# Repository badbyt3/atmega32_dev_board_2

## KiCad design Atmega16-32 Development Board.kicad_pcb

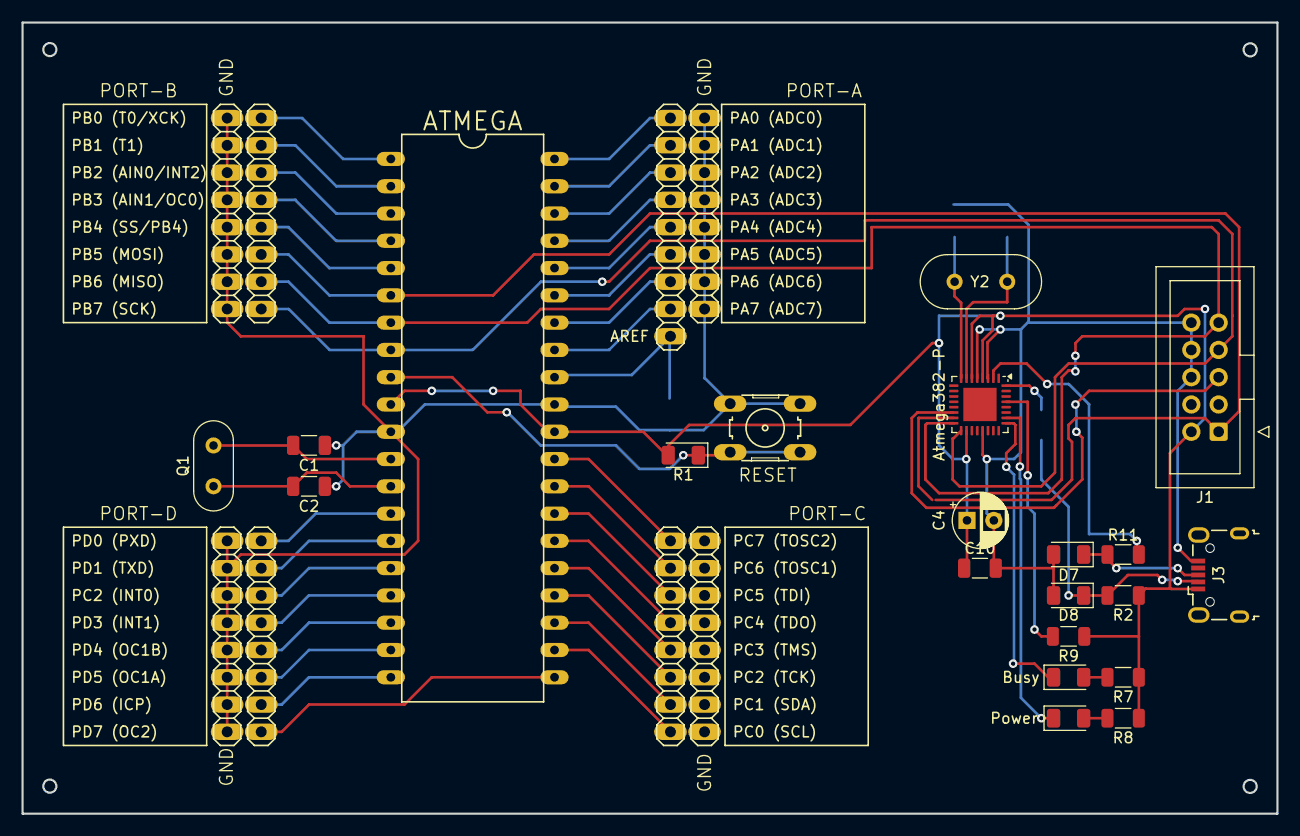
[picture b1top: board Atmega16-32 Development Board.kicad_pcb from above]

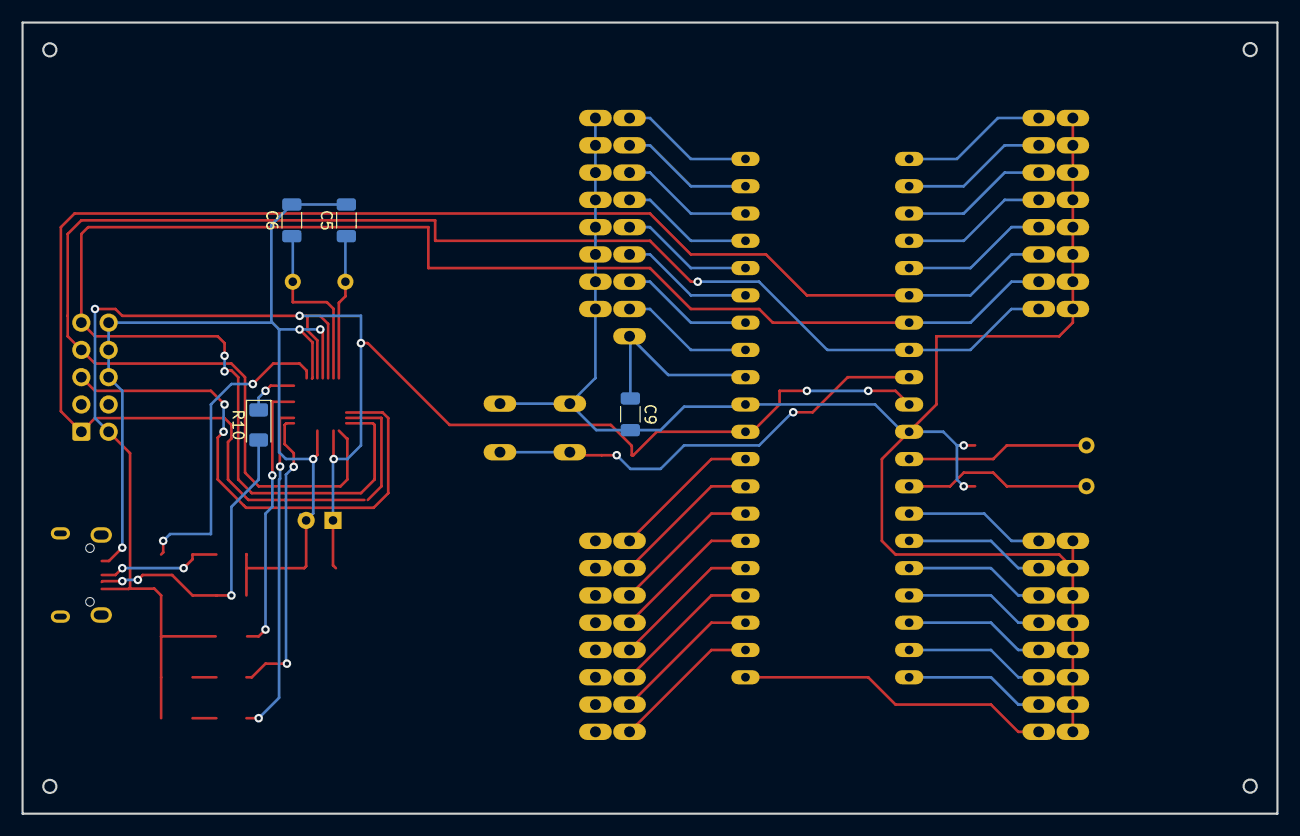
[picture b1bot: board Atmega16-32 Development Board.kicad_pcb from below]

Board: 2 copper layers, 116.8 x 73.7 mm, 33 parts (4 on the bottom side), 49 nets.

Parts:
ATMEGA: MEGA32-P; DIL40
Atmega382-P: ATmega328-M; QFN-32-1EP_5x5mm_P0.5mm_EP3.1x3.1mm
Busy: Busy; LED_1206_3216Metric
C1, C2: C; C_1206_3216Metric
C4: 100uF; CP_Radial_D5.0mm_P2.50mm
C5, C6: 22pF; C_1206_3216Metric
C9: 100n; C_1206_3216Metric
C10: 0.1uF; C_1206_3216Metric
D7, D8: 3V6; D_1206_3216Metric
GND: PINHD-1X8; 1X08
GND#2, GND#3, GND#4: PINHD-1X8; 1X08
J1: ISPHeader; IDC-Header_2x05_P2.54mm_Vertical
J3: USB_B_Micro; USB_Micro-B_Wuerth_629105150521
PORT-A: PINHD-1X9; 1X09
PORT-B: PINHD-1X8; 1X08
PORT-C: PINHD-1X8; 1X08
PORT-D: PINHD-1X8; 1X08
Power: Power; LED_1206_3216Metric
Q1: CRYSTAL; Crystal_HC52-U_Vertical
R1: 10k; D_1206_3216Metric
R2, R7, R8: 1K5; R_1206_3216Metric
R9: 10K; R_1206_3216Metric
R10: 68; D_1206_3216Metric
R11: 68; R_1206_3216Metric
RESET: SWITCH; B3F-10XX
Y2: 12MHz; Crystal_HC18-U_Vertical

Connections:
+5V: ATMEGA.10 (VCC), ATMEGA.30 (AVCC), Atmega382-P.4 (VCC), Atmega382-P.6 (VCC), Atmega382-P.18 (AVCC), C4.1, C10.1, J1.2 (VTG), J3.1 (VBUS), R1.2, R2.1, R7.1, R8.1, R9.1
/AREF: ATMEGA.32 (AREF), C9.1, PORT-A.1
/MISO: ATMEGA.7 ((MISO)PB6), Atmega382-P.16 (PB4), J1.9 (MISO), PORT-B.7
/MOSI: ATMEGA.6 ((MOSI)PB5), Atmega382-P.15 (PB3), J1.1 (MOSI), PORT-B.6
/RESET: ATMEGA.9 (RESET), Atmega382-P.14 (PB2), J1.5 (RST), R1.1, RESET.1 (S), RESET.2 (S1)
/SCK: ATMEGA.8 ((SCK)PB7), Atmega382-P.17 (PB5), J1.7 (SCK), PORT-B.8
GND: ATMEGA.11 (GND), ATMEGA.31 (GND@1), Atmega382-P.3 (GND), Atmega382-P.5 (GND), Atmega382-P.21 (GND), Atmega382-P.33 (GND), C1.1, C2.1, C4.2, C5.2, C6.2, C9.2, C10.2, D7.2 (A), D8.2 (A), GND.1, GND.2, GND.3, GND.4, GND.5, GND.6, GND.7, GND.8, GND#2.1, GND#2.2, GND#2.3, GND#2.4, GND#2.5, GND#2.6, GND#2.7, GND#2.8, GND#3.1, GND#3.2, GND#3.3, GND#3.4, GND#3.5, GND#3.6, GND#3.7, GND#3.8, GND#4.1, GND#4.2, GND#4.3, GND#4.4, GND#4.5, GND#4.6, GND#4.7, GND#4.8, J1.6 (GND), J1.8 (GND), J1.10 (GND), J3.5 (GND), RESET.3, RESET.4 (P1)
unnamed: ATMEGA.40 ((ADC0)PA0), PORT-A.9
unnamed: ATMEGA.39 ((ADC1)PA1), PORT-A.8
unnamed: ATMEGA.38 ((ADC2)PA2), PORT-A.7
unnamed: ATMEGA.37 ((ADC3)PA3), PORT-A.6
unnamed: ATMEGA.36 ((ADC4)PA4), PORT-A.5
unnamed: ATMEGA.35 ((ADC5)PA5), PORT-A.4
unnamed: ATMEGA.34 ((ADC6)PA6), PORT-A.3
unnamed: ATMEGA.33 ((ADC7)PA7), PORT-A.2
unnamed: ATMEGA.3 ((AIN0/INT2)PB2), PORT-B.3
unnamed: ATMEGA.4 ((AIN1/OC0)PB3), PORT-B.4
unnamed: ATMEGA.20 ((ICP)PD6), PORT-D.7
unnamed: ATMEGA.16 ((INT0)PD2), PORT-D.3
unnamed: ATMEGA.17 ((INT1)PD3), PORT-D.4
unnamed: ATMEGA.19 ((OC1A)PD5), PORT-D.6
unnamed: ATMEGA.18 ((OC1B)PD4), PORT-D.5
unnamed: ATMEGA.21 ((OC2)PD7), PORT-D.8
unnamed: ATMEGA.14 ((RXD)PD0), PORT-D.1
unnamed: ATMEGA.22 ((SCL)PC0), PORT-C.1
unnamed: ATMEGA.23 ((SDA)PC1), PORT-C.2
unnamed: ATMEGA.5 ((SS)PB4), PORT-B.5
unnamed: ATMEGA.1 ((T0/XCK)PB0), PORT-B.1
unnamed: ATMEGA.2 ((T1)PB1), PORT-B.2
unnamed: ATMEGA.24 ((TCK)PC2), PORT-C.3
unnamed: ATMEGA.27 ((TDI)PC5), PORT-C.6
unnamed: ATMEGA.26 ((TDO)PC4), PORT-C.5
unnamed: ATMEGA.25 ((TMS)PC3), PORT-C.4
unnamed: ATMEGA.28 ((TOSC1)PC6), PORT-C.7
unnamed: ATMEGA.29 ((TOSC2)PC7), PORT-C.8
unnamed: ATMEGA.15 ((TXD)PD1), PORT-D.2
unnamed: ATMEGA.13 (XTAL1), C2.2, Q1.1
unnamed: ATMEGA.12 (XTAL2), C1.2, Q1.2
unnamed: Busy.2 (A), R7.2
unnamed: Atmega382-P.25 (PC2), Busy.1 (K)
unnamed: Power.2 (A), R8.2
unnamed: Atmega382-P.26 (PC3), Power.1 (K)
unnamed: D7.1 (K), J3.3 (D+), R11.1
unnamed: D8.1 (K), J3.2 (D-), R2.2, R10.2
unnamed: Atmega382-P.32 (PD2), R10.1
unnamed: Atmega382-P.2 (PD4), R11.2
unnamed: Atmega382-P.7 (XTAL1/PB6), C6.1, Y2.2
unnamed: Atmega382-P.8 (XTAL2/PB7), C5.1, Y2.1
unnamed: Atmega382-P.29 (~RESET/PC6), R9.2

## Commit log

2024-06-06 Initial board commit
    Commit contains the development board with the USBasp interface.
